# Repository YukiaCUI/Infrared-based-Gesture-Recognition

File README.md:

# Infrared-based-Gesture-Recognition
Infrared-based Gesture Recognition

This repositories introduces "Comprehensive Design and Practice A Comprehensive Experiment (IV)" focusing on the design of a gesture recognizer based on STM32G0 and infrared reflection sensors. Starting with the design requirements for gesture recognition, it elaborates on the implementation process from two main aspects: hardware circuitry and software programming, ultimately presenting the achieved results.

# Schematic Diagram

# Flowchart

# PCB

# Demo
[Demo](Demo.mp4)

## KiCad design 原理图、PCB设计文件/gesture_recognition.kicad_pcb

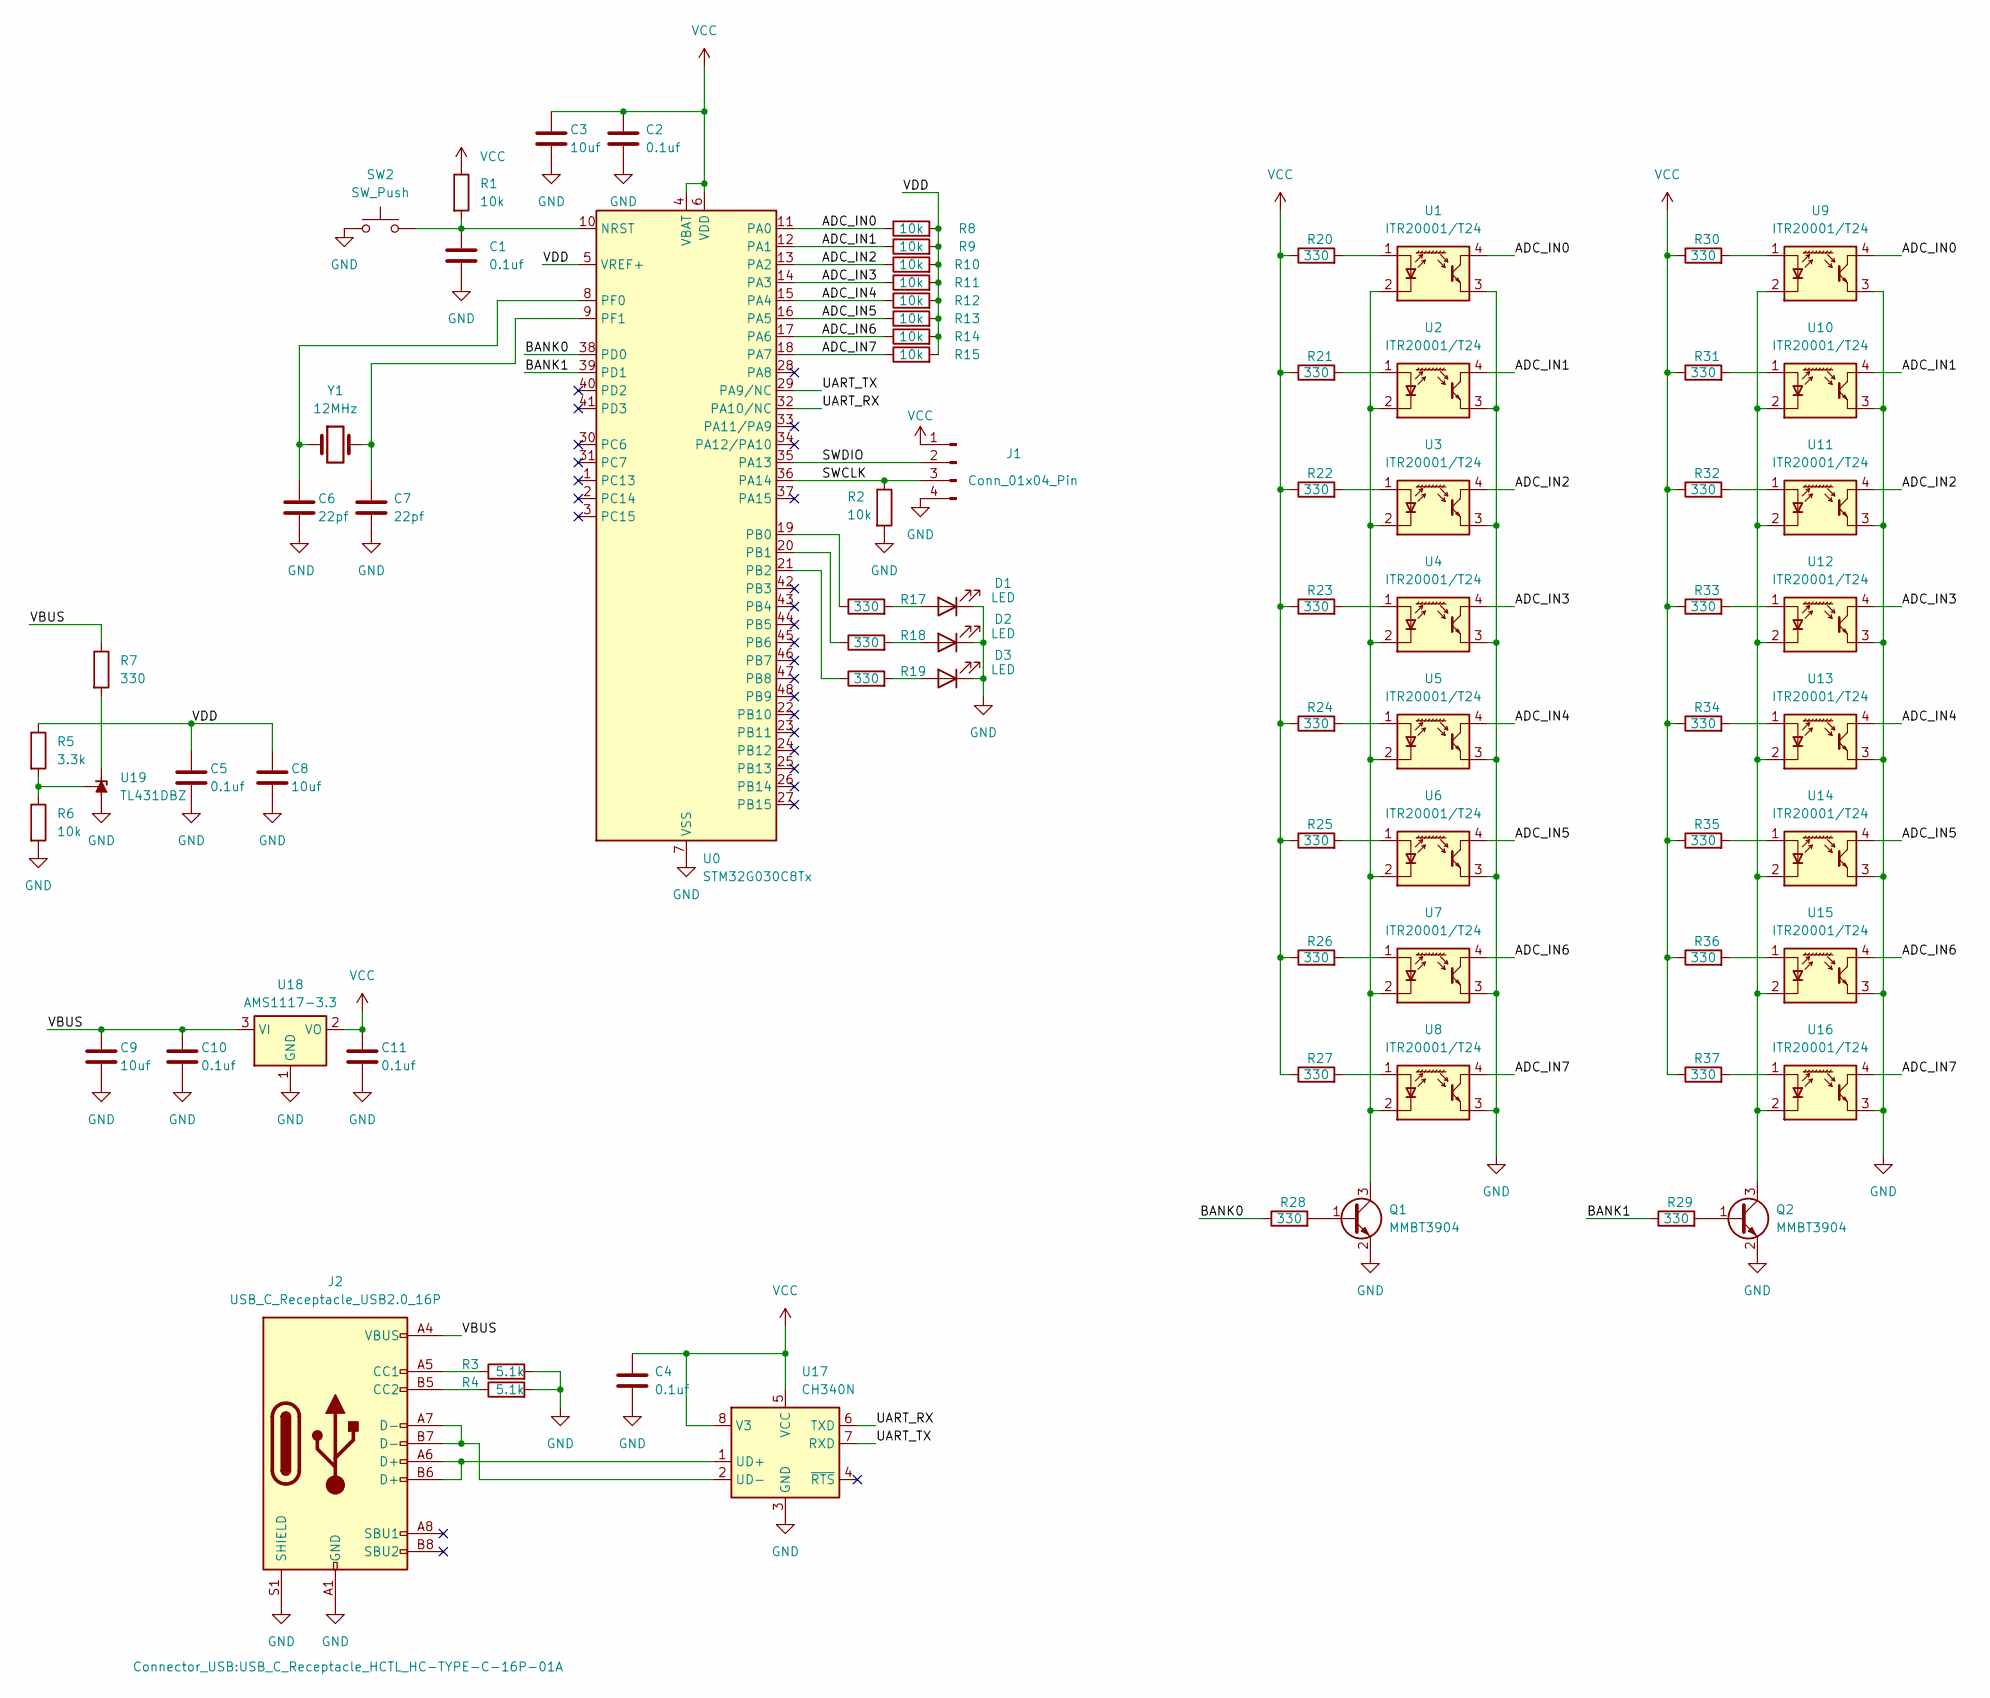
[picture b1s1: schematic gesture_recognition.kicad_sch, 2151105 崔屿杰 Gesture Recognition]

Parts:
C1, C2, C4, C5, C10, C11: 0.1uf; C_0805_2012Metric_Pad1.18x1.45mm_HandSolder
C3, C8, C9: 10uf; C_0805_2012Metric_Pad1.18x1.45mm_HandSolder
C6, C7: 22pf; C_0805_2012Metric_Pad1.18x1.45mm_HandSolder
D1, D2, D3: LED; LED_0805_2012Metric_Pad1.15x1.40mm_HandSolder
J1: Conn_01x04_Pin; FanPinHeader_1x04_P2.54mm_Vertical
J2: USB_C_Receptacle_USB2.0_16P; USB_C_Receptacle_HCTL_HC-TYPE-C-16P-01A
Q1, Q2: MMBT3904; SOT-23_Handsoldering
R1, R2, R6, R8, R9, R10, R11, R12, R13, R14, R15: 10k; R_0805_2012Metric_Pad1.20x1.40mm_HandSolder
R3, R4: 5.1k; R_0805_2012Metric_Pad1.20x1.40mm_HandSolder
R5: 3.3k; R_0805_2012Metric_Pad1.20x1.40mm_HandSolder
R7, R17, R18, R19, R20, R21, R22, R23, R24, R25, R26, R27, R28, R29, R30, R31, R32, R33, R34, R35, R36, R37: 330; R_0805_2012Metric_Pad1.20x1.40mm_HandSolder
SW2: SW_Push; SW_PUSH_6mm
U0: STM32G030C8Tx; LQFP-48_7x7mm_P0.5mm
U1, U2, U3, U4, U5, U6, U7, U8, U9, U10, U11, U12, U13, U14, U15, U16: ITR20001/T24; Everlight_ITR20001
U17: CH340N; SOIC-8_3.9x4.9mm_P1.27mm
U18: AMS1117-3.3; SOT-223-3_TabPin2
U19: TL431DBZ; SOT-23_Handsoldering
Y1: 12MHz; Crystal_SMD_5032-2Pin_5.0x3.2mm_HandSoldering

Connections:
/ADC_IN0: R8.1, U0.11 (PA0), U1.4 (C), U9.4 (C)
/ADC_IN1: R9.1, U0.12 (PA1), U2.4 (C), U10.4 (C)
/ADC_IN2: R10.1, U0.13 (PA2), U3.4 (C), U11.4 (C)
/ADC_IN3: R11.1, U0.14 (PA3), U4.4 (C), U12.4 (C)
/ADC_IN4: R12.1, U0.15 (PA4), U5.4 (C), U13.4 (C)
/ADC_IN5: R13.1, U0.16 (PA5), U6.4 (C), U14.4 (C)
/ADC_IN6: R14.1, U0.17 (PA6), U7.4 (C), U15.4 (C)
/ADC_IN7: R15.1, U0.18 (PA7), U8.4 (C), U16.4 (C)
/BANK0: R28.1, U0.38 (PD0)
/BANK1: R29.1, U0.39 (PD1)
/SWCLK: J1.3, R2.1, U0.36 (PA14)
/SWDIO: J1.2, U0.35 (PA13)
/UART_RX: U0.32 (PA10/NC), U17.6 (TXD)
/UART_TX: U0.29 (PA9/NC), U17.7 (RXD)
/VBUS: C9.1, C10.1, J2.A4 (VBUS), J2.A9 (VBUS), J2.B4 (VBUS), J2.B9 (VBUS), R7.1, U18.3 (VI)
/VDD: C5.1, C8.1, R5.1, R8.2, R9.2, R10.2, R11.2, R12.2, R13.2, R14.2, R15.2, U0.5 (VREF+)
GND: C1.2, C2.2, C3.2, C4.2, C5.2, C6.2, C7.2, C8.2, C9.2, C10.2, C11.2, D1.1 (K), D2.1 (K), D3.1 (K), J1.4, J2.A1 (GND), J2.A12 (GND), J2.B1 (GND), J2.B12 (GND), J2.S1 (SHIELD), Q1.2 (E), Q2.2 (E), R2.2, R3.2, R4.2, R6.2, SW2.1, U0.7 (VSS), U1.3 (E), U2.3 (E), U3.3 (E), U4.3 (E), U5.3 (E), U6.3 (E), U7.3 (E), U8.3 (E), U9.3 (E), U10.3 (E), U11.3 (E), U12.3 (E), U13.3 (E), U14.3 (E), U15.3 (E), U16.3 (E), U17.3 (GND), U18.1 (GND), U19.3 (A)
unnamed: D1.2 (A), R17.2
unnamed: D2.2 (A), R18.2
unnamed: D3.2 (A), R19.2
unnamed: J2.A5 (CC1), R3.1
unnamed: J2.B5 (CC2), R4.1
unnamed: Q1.1 (B), R28.2
unnamed: Q1.3 (C), U1.2 (K), U2.2 (K), U3.2 (K), U4.2 (K), U5.2 (K), U6.2 (K), U7.2 (K), U8.2 (K)
unnamed: Q2.1 (B), R29.2
unnamed: Q2.3 (C), U9.2 (K), U10.2 (K), U11.2 (K), U12.2 (K), U13.2 (K), U14.2 (K), U15.2 (K), U16.2 (K)
unnamed: C1.1, R1.2, SW2.2, U0.10 (NRST)
unnamed: R17.1, U0.19 (PB0)
unnamed: R18.1, U0.20 (PB1)
unnamed: R19.1, U0.21 (PB2)
unnamed: C6.1, U0.8 (PF0), Y1.1
unnamed: C7.1, U0.9 (PF1), Y1.2
unnamed: R20.2, U1.1 (A)
unnamed: R21.2, U2.1 (A)
unnamed: R22.2, U3.1 (A)
unnamed: R23.2, U4.1 (A)
unnamed: R24.2, U5.1 (A)
unnamed: R25.2, U6.1 (A)
unnamed: R26.2, U7.1 (A)
unnamed: R27.2, U8.1 (A)
unnamed: R30.2, U9.1 (A)
unnamed: R31.2, U10.1 (A)
unnamed: R32.2, U11.1 (A)
unnamed: R33.2, U12.1 (A)
unnamed: R34.2, U13.1 (A)
unnamed: R35.2, U14.1 (A)
unnamed: R36.2, U15.1 (A)
unnamed: R37.2, U16.1 (A)
unnamed: J2.A6 (D+), J2.B6 (D+), U17.1 (UD+)
unnamed: J2.A7 (D-), J2.B7 (D-), U17.2 (UD-)
unnamed: R7.2, U19.1 (K)
unnamed: R5.2, R6.1, U19.2 (REF)
VCC: C2.1, C3.1, C4.1, C11.1, J1.1, R1.1, R20.1, R21.1, R22.1, R23.1, R24.1, R25.1, R26.1, R27.1, R30.1, R31.1, R32.1, R33.1, R34.1, R35.1, R36.1, R37.1, U0.4 (VBAT), U0.6 (VDD), U17.5 (VCC), U17.8 (V3), U18.2 (VO)

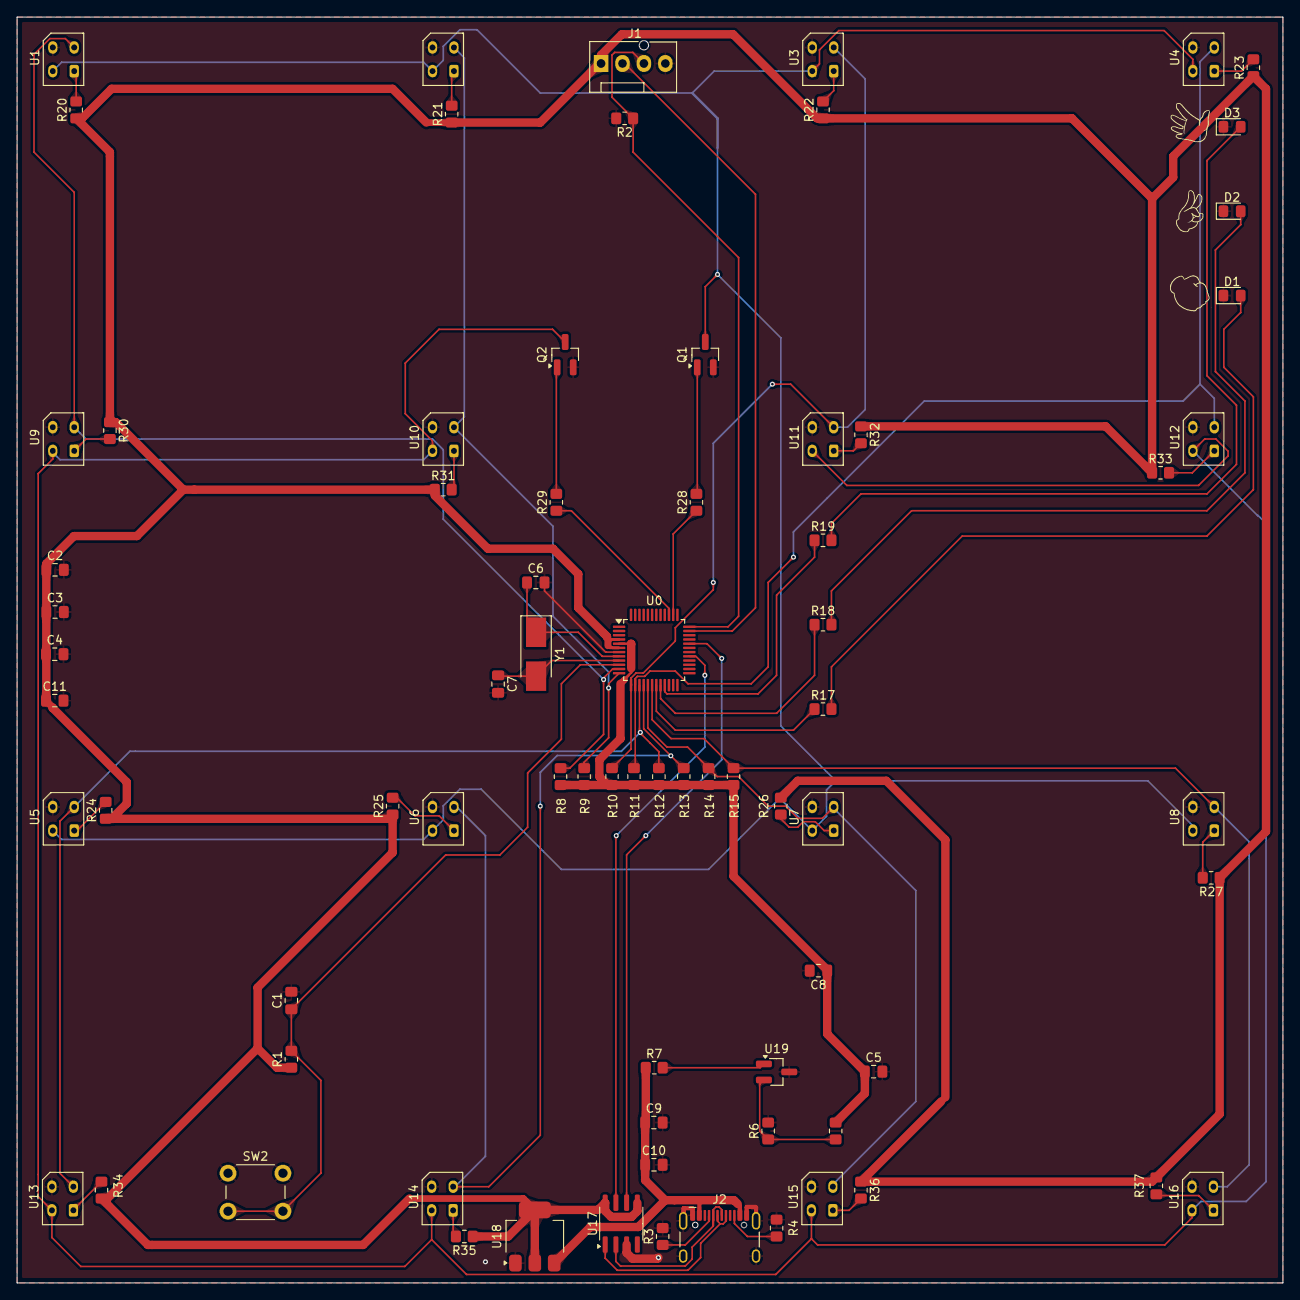
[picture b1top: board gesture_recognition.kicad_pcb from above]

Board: 2 copper layers, 150.0 x 150.0 mm, 77 parts (0 on the bottom side), 53 nets.

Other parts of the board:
布: LOGO

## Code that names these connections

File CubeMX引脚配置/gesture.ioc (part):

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Mcu.Name=STM32G030C(6-8)Tx
Mcu.Package=LQFP48
Mcu.UserName=STM32G030C8Tx
PA0.Mode=IN0
PA0.Signal=ADC1_IN0
PA1.Mode=IN1
PA1.Signal=ADC1_IN1
PA10.Mode=Asynchronous
PA10.Signal=USART1_RX
PA13.Mode=Serial_Wire
PA13.Signal=SYS_SWDIO
PA14-BOOT0.Mode=Serial_Wire
PA14-BOOT0.Signal=SYS_SWCLK
PA2.Mode=IN2
PA2.Signal=ADC1_IN2
PA3.Mode=IN3
PA3.Signal=ADC1_IN3
PA4.Mode=IN4
PA4.Signal=ADC1_IN4
PA5.Mode=IN5
PA5.Signal=ADC1_IN5
PA6.Mode=IN6
PA6.Signal=ADC1_IN6
PA7.Mode=IN7
PA7.Signal=ADC1_IN7
PA9.Mode=Asynchronous
PA9.Signal=USART1_TX
PB0.GPIOParameters=GPIO_Label
PB0.GPIO_Label=LED0
PB0.Signal=GPIO_Output
PB1.GPIOParameters=GPIO_Label
PB1.GPIO_Label=LED1
PB1.Signal=GPIO_Output
PB2.GPIOParameters=GPIO_Label
PB2.GPIO_Label=LED2
PB2.Signal=GPIO_Output
PD0.GPIOParameters=GPIO_Label
PD0.GPIO_Label=BANK0
PD0.Signal=GPIO_Output
PD1.GPIOParameters=GPIO_Label
PD1.GPIO_Label=BANK1
PD1.Signal=GPIO_Output
RCC.HSE_VALUE=8000000
RCC.SYSCLKFreq_VALUE=64000000
RCC.SYSCLKSource=RCC_SYSCLKSOURCE_PLLCLK
board=custom

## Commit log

2024-12-01 archive
2024-12-01 Demo
